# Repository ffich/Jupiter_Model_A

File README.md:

# Jupiter System
The Jupiter System is a system developed to leverage SW capabilities of Raspberry PI Compute Modules, by designing a system with an high level of HW configurability and scalability. This allows to use the power of the existing SW ecosystem in conjunction with a modular and scalable HW system, so that the user can take benefits from both of them. This HW configurability and expandability is given by adopting built-in sockets for some common peripheral add-on’s standard. The selected standards are the Mikroelektronika MikroBUS, the SeedStudio Grove and the Sparkfun QWIIC, which are widely used and open standards for HW expandability. The adherence to those standards allows the Jupiter System boards to be able to connect to the various expansion and breakout boards currently available on the market. These boards contain various types of sensor, actuators and interfaces, allowing for a very high level of HW scalability and modularity.

In this perspective the Jupiter System acts like a bridge between the Raspberry Pi SW and the HW world, allowing to take benefit from both the ecosystems.

Examples of application fields of Jupiter System are:
- Home automation System,
- IoT applications,
- Connectivity Applications,
- Monitoring and control Systems,
- Remote Control,
- Industrial Process control,
- Robotics applications,
- Test benches,
- Etc…

[youtube.com/watch?v=70Tqia20eaI](https://www.youtube.com/watch?v=70Tqia20eaI)

[youtube.com/watch?v=70Tqia20eaI](https://www.youtube.com/watch?v=70Tqia20eaI)

# Jupiter Model A
The Jupiter Model A is the desktop-version Jupiter board. It allows the user to experiment with the full potential of the Jupiter System. It's compatible with Raspberry CM3 and CM3+ (as the Raspberry Pi fundation does, we also strongly recommend to use CM3+ for newer design) and, among other peripherals, the board has 4 MikroBUS, 2 Grove and 2 Qwiic sockets that allow to create countless of combinations with Click, Grove or Qwiic slave devices.

# MikroE Click Boards
There are more that 1000 click boards currently available on the market, and so many applications can be realized exploiting the power of raspberry (on SW side) and the high availability and modularity of the click boards (on the HW side).
For more information on click boards, please refer to the Mikroe website: https://www.mikroe.com/click

# Board Description
The HW block diagram of the Jupiter Model A is depicted below. As is possible to see, the brain of the system is a Raspberry PI compute module 3 or 3+, connected to a broad list of peripherals. 

More in details, the board is populated with:
-	3x USB
-	1x WiFi
-	1x CSI Interface
-	1x DSI interface
-	1x Boot SD card Socket
-	1x Serial Port
-	Up to 16 GPIO
-	4x User LEDs
-	2x User Buttons

Additionally the board contains 4 MikroBUS Sockets that allow to interface with MikroBUS compatible devices, like the click boards, 2 Groove and 2 QWIIC connectors.

# Examples of combination with Click Boards

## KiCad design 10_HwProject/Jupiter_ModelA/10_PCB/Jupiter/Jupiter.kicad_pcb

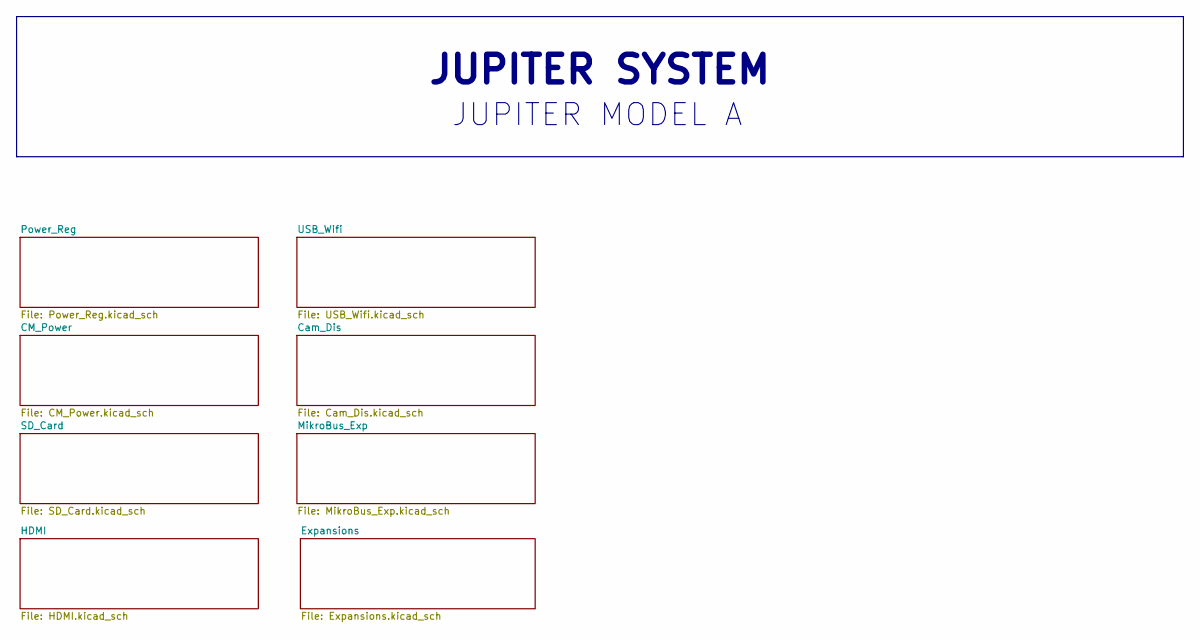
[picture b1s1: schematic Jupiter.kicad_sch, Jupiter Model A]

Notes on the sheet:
JUPITER SYSTEM
JUPITER MODEL A

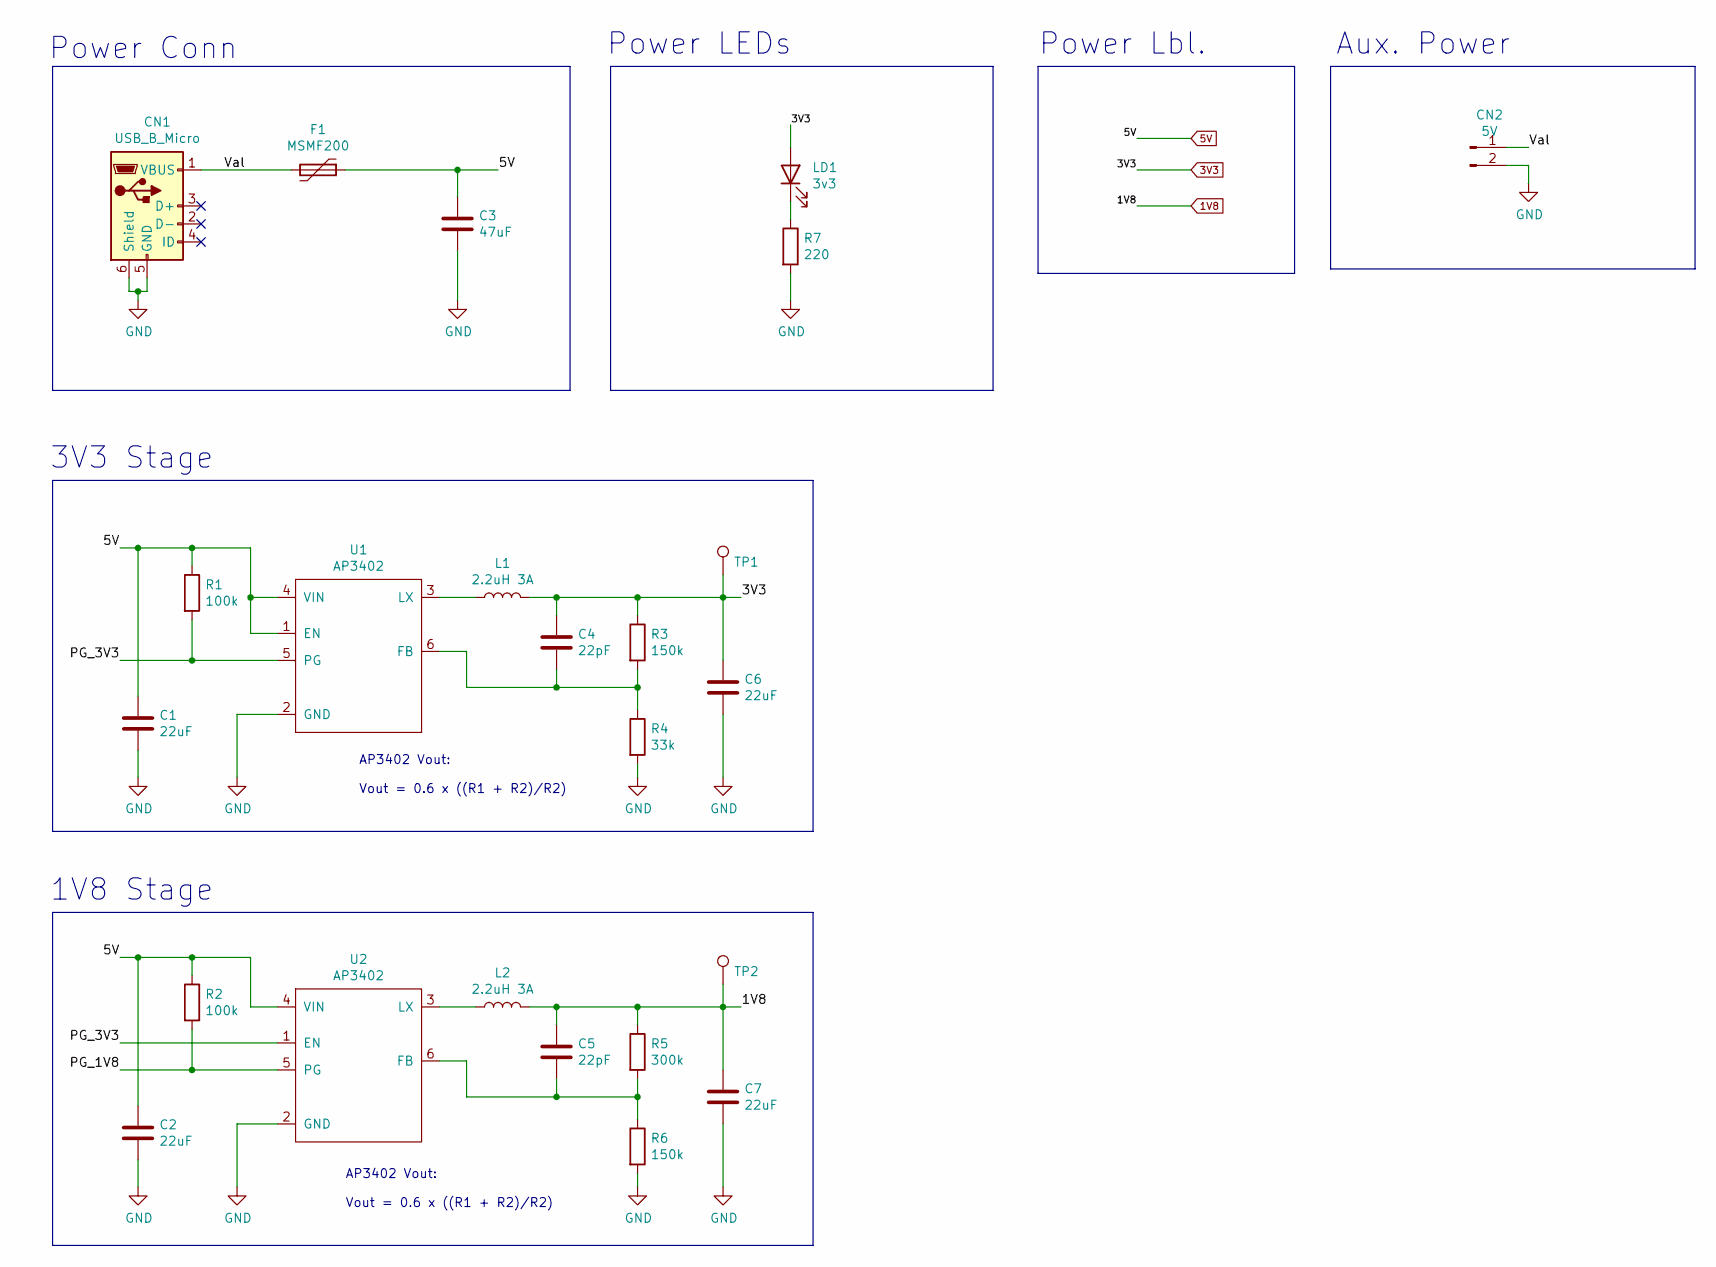
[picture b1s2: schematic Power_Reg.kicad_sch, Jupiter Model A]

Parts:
C1, C2, C6, C7: 22uF; C_0805_2012Metric
C3: 47uF; C_1206_3216Metric
C4, C5: 22pF; C_0603_1608Metric
CN1: USB_B_Micro; USB_Micro-B_Molex_47346-0001
CN2: 5V; PinHeader_1x02_P2.54mm_Vertical
F1: MSMF200; Fuse_1812_4532Metric
L1, L2: 2.2uH 3A; L_Sunlord_MWSA0518_5.4x5.2mm
LD1: 3v3; LED_0805_2012Metric
R1, R2: 100k; R_0603_1608Metric
R3, R6: 150k; R_0603_1608Metric
R4: 33k; R_0603_1608Metric
R5: 300k; R_0603_1608Metric
R7: 220; R_0603_1608Metric
TP1, TP2: TestPoint_Pad_D1.0mm
U1, U2: AP3402; TSOT-23-6

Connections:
1V8: C5.1, C7.1, L2.2, R5.1, TP2.1; also elsewhere on the board
3V3: C4.1, C6.1, L1.2, LD1.2 (A), R3.1, TP1.1; also elsewhere on the board
5V: C1.1, C2.1, C3.1, F1.1, R1.1, R2.1, U1.1 (EN), U1.4 (VIN), U2.4 (VIN); also elsewhere on the board
/Power_Reg/PG_1V8: R2.2, U2.5 (PG)
/Power_Reg/PG_3V3: R1.2, U1.5 (PG), U2.1 (EN)
/Power_Reg/Val: CN1.1 (VBUS), CN2.1, F1.2
GND: C1.2, C2.2, C3.2, C6.2, C7.2, CN1.5 (GND), CN1.6 (Shield), CN2.2, R4.2, R6.2, R7.2, U1.2 (GND), U2.2 (GND); also elsewhere on the board
unnamed: C4.2, R3.2, R4.1, U1.6 (FB)
unnamed: C5.2, R5.2, R6.1, U2.6 (FB)
unnamed: L1.1, U1.3 (LX)
unnamed: L2.1, U2.3 (LX)
unnamed: LD1.1 (K), R7.1

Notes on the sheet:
AP3402 Vout: Vout = 0.6 x ((R1 + R2)/R2)
Aux. Power
3V3 Stage
Power Lbl.
Power LEDs
Power Conn
1V8 Stage

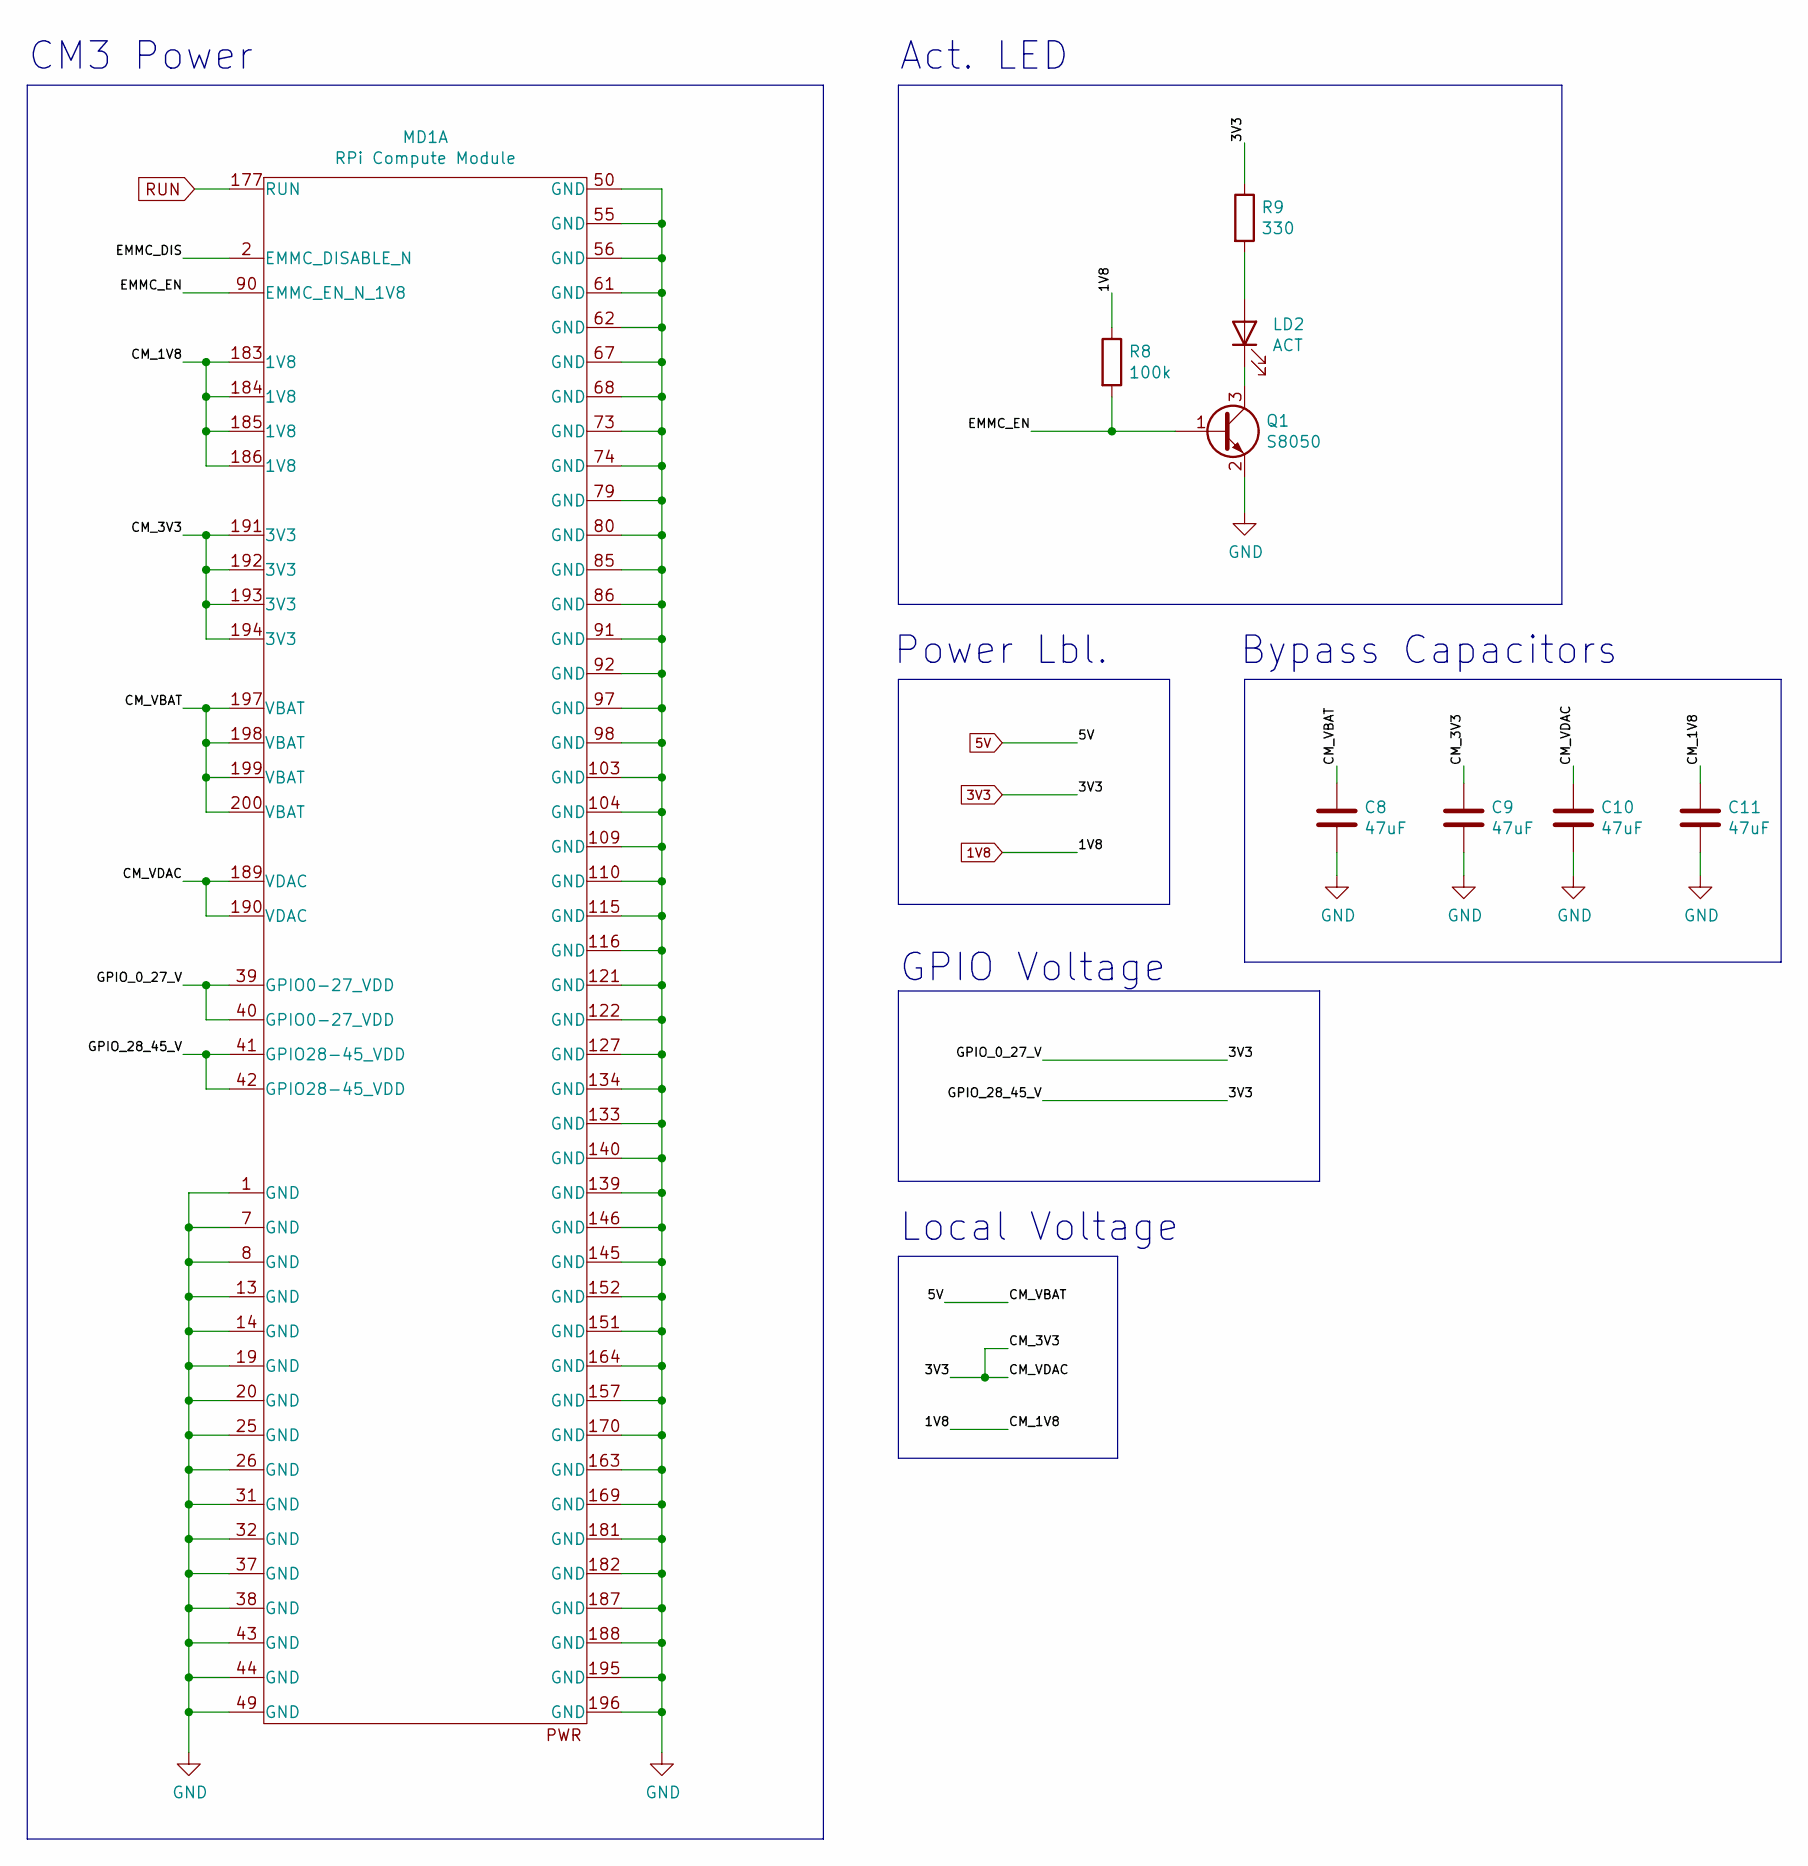
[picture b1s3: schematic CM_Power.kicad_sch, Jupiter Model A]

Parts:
C8, C9, C10, C11: 47uF; C_1206_3216Metric
LD2: ACT; LED_0805_2012Metric
MD1: RPi Compute Module; Conn_TE-DDR2-SODIMM-0.6-200P-doublesided
Q1: S8050; SOT-23
R8: 100k; R_0603_1608Metric
R9: 330; R_0603_1608Metric

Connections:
1V8: C11.1, MD1.183 (1V8), MD1.184 (1V8), MD1.185 (1V8), MD1.186 (1V8), R8.1; also elsewhere on the board
3V3: C9.1, C10.1, MD1.39 (GPIO0-27_VDD), MD1.40 (GPIO0-27_VDD), MD1.41 (GPIO28-45_VDD), MD1.42 (GPIO28-45_VDD), MD1.189 (VDAC), MD1.190 (VDAC), MD1.191 (3V3), MD1.192 (3V3), MD1.193 (3V3), MD1.194 (3V3), R9.1; also elsewhere on the board
5V: C8.1, MD1.197 (VBAT), MD1.198 (VBAT), MD1.199 (VBAT), MD1.200 (VBAT); also elsewhere on the board
/CM_Power/EMMC_DIS: MD1.2 (EMMC_DISABLE_N)
/CM_Power/EMMC_EN: MD1.90 (EMMC_EN_N_1V8), Q1.1 (B), R8.2
GND: C8.2, C9.2, C10.2, C11.2, MD1.1 (GND), MD1.7 (GND), MD1.8 (GND), MD1.13 (GND), MD1.14 (GND), MD1.19 (GND), MD1.20 (GND), MD1.25 (GND), MD1.26 (GND), MD1.31 (GND), MD1.32 (GND), MD1.37 (GND), MD1.38 (GND), MD1.43 (GND), MD1.44 (GND), MD1.49 (GND), MD1.50 (GND), MD1.55 (GND), MD1.56 (GND), MD1.61 (GND), MD1.62 (GND), MD1.67 (GND), MD1.68 (GND), MD1.73 (GND), MD1.74 (GND), MD1.79 (GND), MD1.80 (GND), MD1.85 (GND), MD1.86 (GND), MD1.91 (GND), MD1.92 (GND), MD1.97 (GND), MD1.98 (GND), MD1.103 (GND), MD1.104 (GND), MD1.109 (GND), MD1.110 (GND), MD1.115 (GND), MD1.116 (GND), MD1.121 (GND), MD1.122 (GND), MD1.127 (GND), MD1.133 (GND), MD1.134 (GND), MD1.139 (GND), MD1.140 (GND), MD1.145 (GND), MD1.146 (GND), MD1.151 (GND), MD1.152 (GND), MD1.157 (GND), MD1.163 (GND), MD1.164 (GND), MD1.169 (GND), MD1.170 (GND), MD1.181 (GND), MD1.182 (GND), MD1.187 (GND), MD1.188 (GND), MD1.195 (GND), MD1.196 (GND), Q1.2 (E); also elsewhere on the board
unnamed: LD2.1 (K), Q1.3 (C)
unnamed: LD2.2 (A), R9.2
RUN: MD1.177 (RUN); also elsewhere on the board

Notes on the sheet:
GPIO Voltage
Bypass Capacitors
Power Lbl.
CM3 Power
Act. LED
Local Voltage

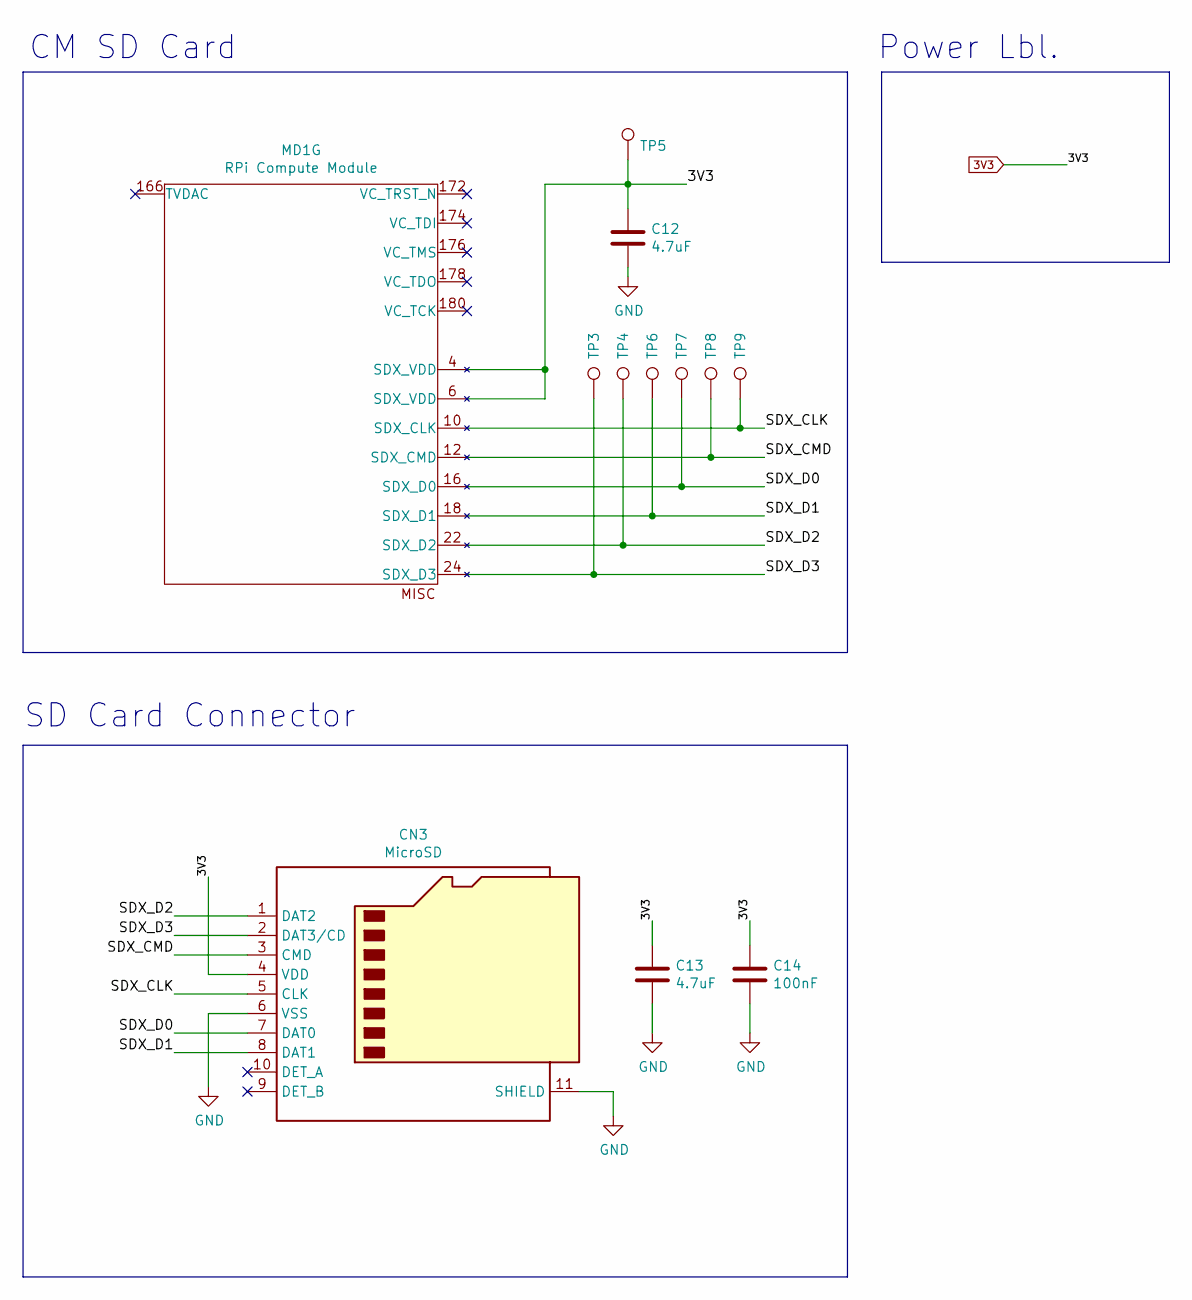
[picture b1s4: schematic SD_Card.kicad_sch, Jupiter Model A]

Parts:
C12, C13: 4.7uF; C_1206_3216Metric
C14: 100nF; C_0805_2012Metric
CN3: MicroSD; microSD_HC_Hirose_DM3D-SF
MD1: RPi Compute Module; Conn_TE-DDR2-SODIMM-0.6-200P-doublesided
TP3, TP4, TP5, TP6, TP7, TP8, TP9: TestPoint_Pad_D1.0mm

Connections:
3V3: C12.1, C13.1, C14.1, CN3.4 (VDD), MD1.4 (SDX_VDD), MD1.6 (SDX_VDD), TP5.1; also elsewhere on the board
/SD_Card/SDX_CLK: CN3.5 (CLK), MD1.10 (SDX_CLK), TP9.1
/SD_Card/SDX_CMD: CN3.3 (CMD), MD1.12 (SDX_CMD), TP8.1
/SD_Card/SDX_D0: CN3.7 (DAT0), MD1.16 (SDX_D0), TP7.1
/SD_Card/SDX_D1: CN3.8 (DAT1), MD1.18 (SDX_D1), TP6.1
/SD_Card/SDX_D2: CN3.1 (DAT2), MD1.22 (SDX_D2), TP4.1
/SD_Card/SDX_D3: CN3.2 (DAT3/CD), MD1.24 (SDX_D3), TP3.1
GND: C12.2, C13.2, C14.2, CN3.6 (VSS), CN3.11 (SHIELD); also elsewhere on the board

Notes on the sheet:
Power Lbl.
SD Card Connector
CM SD Card

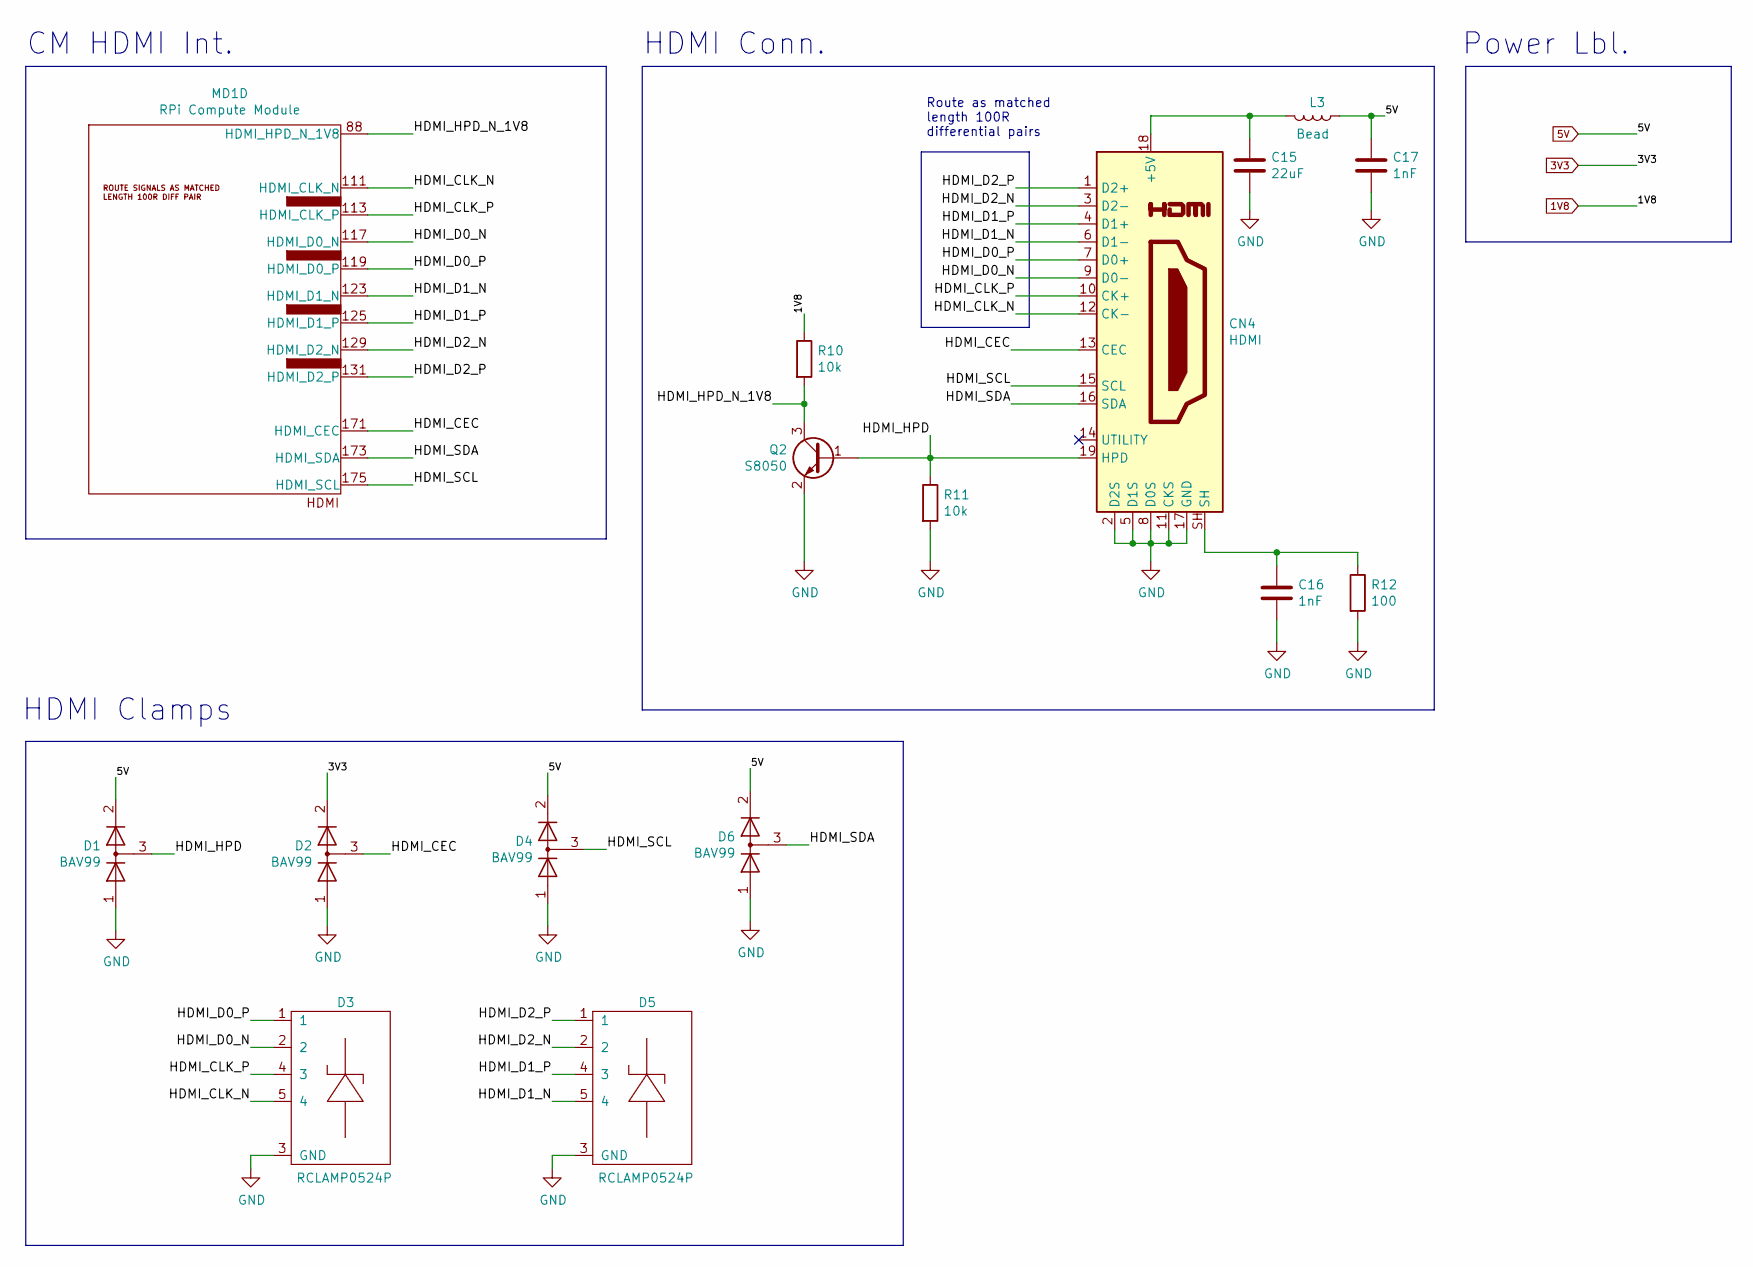
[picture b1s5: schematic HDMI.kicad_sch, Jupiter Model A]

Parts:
C15: 22uF; C_0805_2012Metric
C16: 1nF; C_0603_1608Metric
C17: 1nF; C_0805_2012Metric
CN4: HDMI; HDMI_TypeA
D1, D2, D4, D6: BAV99; SOT-23
D3, D5: RCLAMP0524P
L3: Bead; L_0805_2012Metric
MD1: RPi Compute Module; Conn_TE-DDR2-SODIMM-0.6-200P-doublesided
Q2: S8050; SOT-23
R10, R11: 10k; R_0603_1608Metric
R12: 100; R_0603_1608Metric

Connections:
1V8: R10.1; also elsewhere on the board
3V3: D2.2 (A); also elsewhere on the board
5V: C17.1, D1.2 (A), D4.2 (A), D6.2 (A), L3.1; also elsewhere on the board
/HDMI/HDMI_CEC: CN4.13 (CEC), D2.3 (K), MD1.171 (HDMI_CEC)
/HDMI/HDMI_CLK_N: CN4.12 (CK-), D3.5 (4), MD1.111 (HDMI_CLK_N)
/HDMI/HDMI_CLK_P: CN4.10 (CK+), D3.4 (3), MD1.113 (HDMI_CLK_P)
/HDMI/HDMI_D0_N: CN4.9 (D0-), D3.2, MD1.117 (HDMI_D0_N)
/HDMI/HDMI_D0_P: CN4.7 (D0+), D3.1, MD1.119 (HDMI_D0_P)
/HDMI/HDMI_D1_N: CN4.6 (D1-), D5.5 (4), MD1.123 (HDMI_D1_N)
/HDMI/HDMI_D1_P: CN4.4 (D1+), D5.4 (3), MD1.125 (HDMI_D1_P)
/HDMI/HDMI_D2_N: CN4.3 (D2-), D5.2, MD1.129 (HDMI_D2_N)
/HDMI/HDMI_D2_P: CN4.1 (D2+), D5.1, MD1.131 (HDMI_D2_P)
/HDMI/HDMI_HPD: CN4.19 (HPD), D1.3 (K), Q2.1 (B), R11.1
/HDMI/HDMI_HPD_N_1V8: MD1.88 (HDMI_HPD_N_1V8), Q2.3 (C), R10.2
/HDMI/HDMI_SCL: CN4.15 (SCL), D4.3 (K), MD1.175 (HDMI_SCL)
/HDMI/HDMI_SDA: CN4.16 (SDA), D6.3 (K), MD1.173 (HDMI_SDA)
GND: C15.2, C16.2, C17.2, CN4.2 (D2S), CN4.5 (D1S), CN4.8 (D0S), CN4.11 (CKS), CN4.17 (GND), D1.1 (K), D2.1 (K), D3.3 (GND), D4.1 (K), D5.3 (GND), D6.1 (K), Q2.2 (E), R11.2, R12.2; also elsewhere on the board
unnamed: C15.1, CN4.18 (+5V), L3.2
unnamed: C16.1, CN4.SH, R12.1

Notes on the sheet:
Power Lbl.
Route as matched length 100R differential pairs
HDMI Conn.
CM HDMI Int.
HDMI Clamps

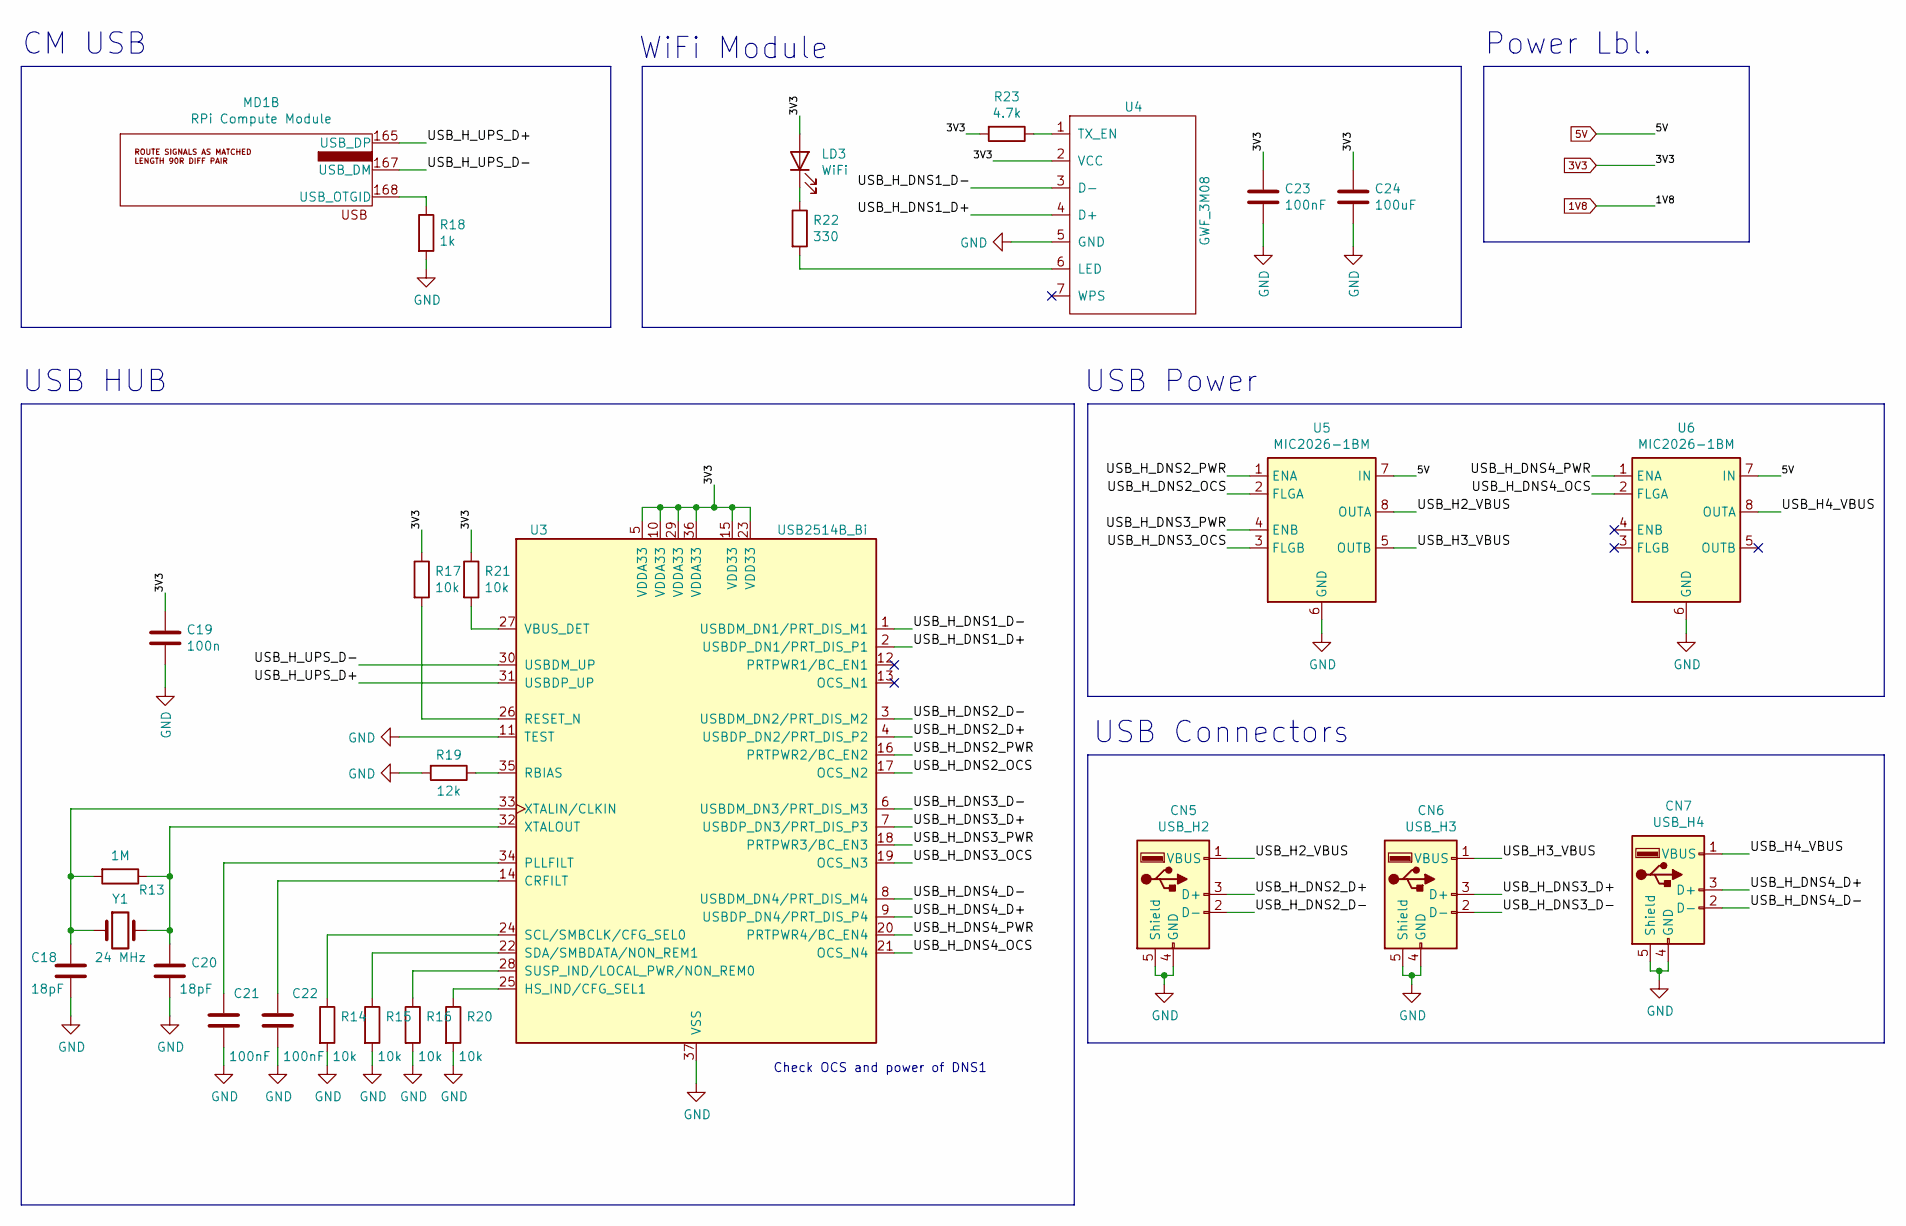
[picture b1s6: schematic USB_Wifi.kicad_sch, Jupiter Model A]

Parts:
C18, C20: 18pF; C_0603_1608Metric
C19: 100n; C_0805_2012Metric
C21, C22, C23: 100nF; C_0805_2012Metric
C24: 100uF; C_1206_3216Metric
CN5: USB_H2; USB_A_Stewart_SS-52100-001_Horizontal
CN6: USB_H3; USB_A_Stewart_SS-52100-001_Horizontal
CN7: USB_H4; USB_A_Stewart_SS-52100-001_Horizontal
LD3: WiFi; LED_0805_2012Metric
MD1: RPi Compute Module; Conn_TE-DDR2-SODIMM-0.6-200P-doublesided
R13: 1M; R_0603_1608Metric
R14, R15, R16, R17, R20, R21: 10k; R_0603_1608Metric
R18: 1k; R_0603_1608Metric
R19: 12k; R_0603_1608Metric
R22: 330; R_0603_1608Metric
R23: 4.7k; R_0603_1608Metric
U3: USB2514B_Bi; QFN-36-1EP_6x6mm_P0.5mm_EP3.7x3.7mm
U4: GWF_3M08; GWF_3M08_WifiModule
U5, U6: MIC2026-1BM; SOIC-8_3.9x4.9mm_P1.27mm
Y1: 24 MHz; Crystal_SMD_5032-2Pin_5.0x3.2mm

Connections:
3V3: C19.1, C23.1, C24.1, LD3.2 (A), R17.1, R21.1, R23.2, U3.5 (VDDA33), U3.10 (VDDA33), U3.15 (VDD33), U3.23 (VDD33), U3.29 (VDDA33), U3.36 (VDDA33), U4.2 (VCC); also elsewhere on the board
5V: U5.7 (IN), U6.7 (IN); also elsewhere on the board
/USB_Wifi/USB_H2_VBUS: CN5.1 (VBUS), U5.8 (OUTA)
/USB_Wifi/USB_H3_VBUS: CN6.1 (VBUS), U5.5 (OUTB)
/USB_Wifi/USB_H4_VBUS: CN7.1 (VBUS), U6.8 (OUTA)
/USB_Wifi/USB_H_DNS1_D+: U3.2 (USBDP_DN1/PRT_DIS_P1), U4.4 (D+)
/USB_Wifi/USB_H_DNS1_D-: U3.1 (USBDM_DN1/PRT_DIS_M1), U4.3 (D-)
/USB_Wifi/USB_H_DNS2_D+: CN5.3 (D+), U3.4 (USBDP_DN2/PRT_DIS_P2)
/USB_Wifi/USB_H_DNS2_D-: CN5.2 (D-), U3.3 (USBDM_DN2/PRT_DIS_M2)
/USB_Wifi/USB_H_DNS2_OCS: U3.17 (OCS_N2), U5.2 (FLGA)
/USB_Wifi/USB_H_DNS2_PWR: U3.16 (PRTPWR2/BC_EN2), U5.1 (ENA)
/USB_Wifi/USB_H_DNS3_D+: CN6.3 (D+), U3.7 (USBDP_DN3/PRT_DIS_P3)
/USB_Wifi/USB_H_DNS3_D-: CN6.2 (D-), U3.6 (USBDM_DN3/PRT_DIS_M3)
/USB_Wifi/USB_H_DNS3_OCS: U3.19 (OCS_N3), U5.3 (FLGB)
/USB_Wifi/USB_H_DNS3_PWR: U3.18 (PRTPWR3/BC_EN3), U5.4 (ENB)
/USB_Wifi/USB_H_DNS4_D+: CN7.3 (D+), U3.9 (USBDP_DN4/PRT_DIS_P4)
/USB_Wifi/USB_H_DNS4_D-: CN7.2 (D-), U3.8 (USBDM_DN4/PRT_DIS_M4)
/USB_Wifi/USB_H_DNS4_OCS: U3.21 (OCS_N4), U6.2 (FLGA)
/USB_Wifi/USB_H_DNS4_PWR: U3.20 (PRTPWR4/BC_EN4), U6.1 (ENA)
/USB_Wifi/USB_H_UPS_D+: MD1.165 (USB_DP), U3.31 (USBDP_UP)
/USB_Wifi/USB_H_UPS_D-: MD1.167 (USB_DM), U3.30 (USBDM_UP)
GND: C18.2, C19.2, C20.2, C21.2, C22.2, C23.2, C24.2, CN5.4 (GND), CN5.5 (Shield), CN6.4 (GND), CN6.5 (Shield), CN7.4 (GND), CN7.5 (Shield), R14.2, R15.2, R16.2, R18.2, R19.2, R20.2, U3.11 (TEST), U3.37 (VSS), U4.5 (GND), U5.6 (GND), U6.6 (GND); also elsewhere on the board
unnamed: C18.1, R13.2, U3.33 (XTALIN/CLKIN), Y1.1
unnamed: C20.1, R13.1, U3.32 (XTALOUT), Y1.2
unnamed: C21.1, U3.34 (PLLFILT)
unnamed: C22.1, U3.14 (CRFILT)
unnamed: LD3.1 (K), R22.1
unnamed: MD1.168 (USB_OTGID), R18.1
unnamed: R14.1, U3.24 (SCL/SMBCLK/CFG_SEL0)
unnamed: R15.1, U3.22 (SDA/SMBDATA/NON_REM1)
unnamed: R16.1, U3.28 (SUSP_IND/LOCAL_PWR/NON_REM0)
unnamed: R17.2, U3.26 (RESET_N)
unnamed: R19.1, U3.35 (RBIAS)
unnamed: R20.1, U3.25 (HS_IND/CFG_SEL1)
unnamed: R21.2, U3.27 (VBUS_DET)
unnamed: R22.2, U4.6 (LED)
unnamed: R23.1, U4.1 (TX_EN)

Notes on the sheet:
WiFi Module
USB Power
CM USB
Power Lbl.
USB HUB
Check OCS and power of DNS1
USB Connectors

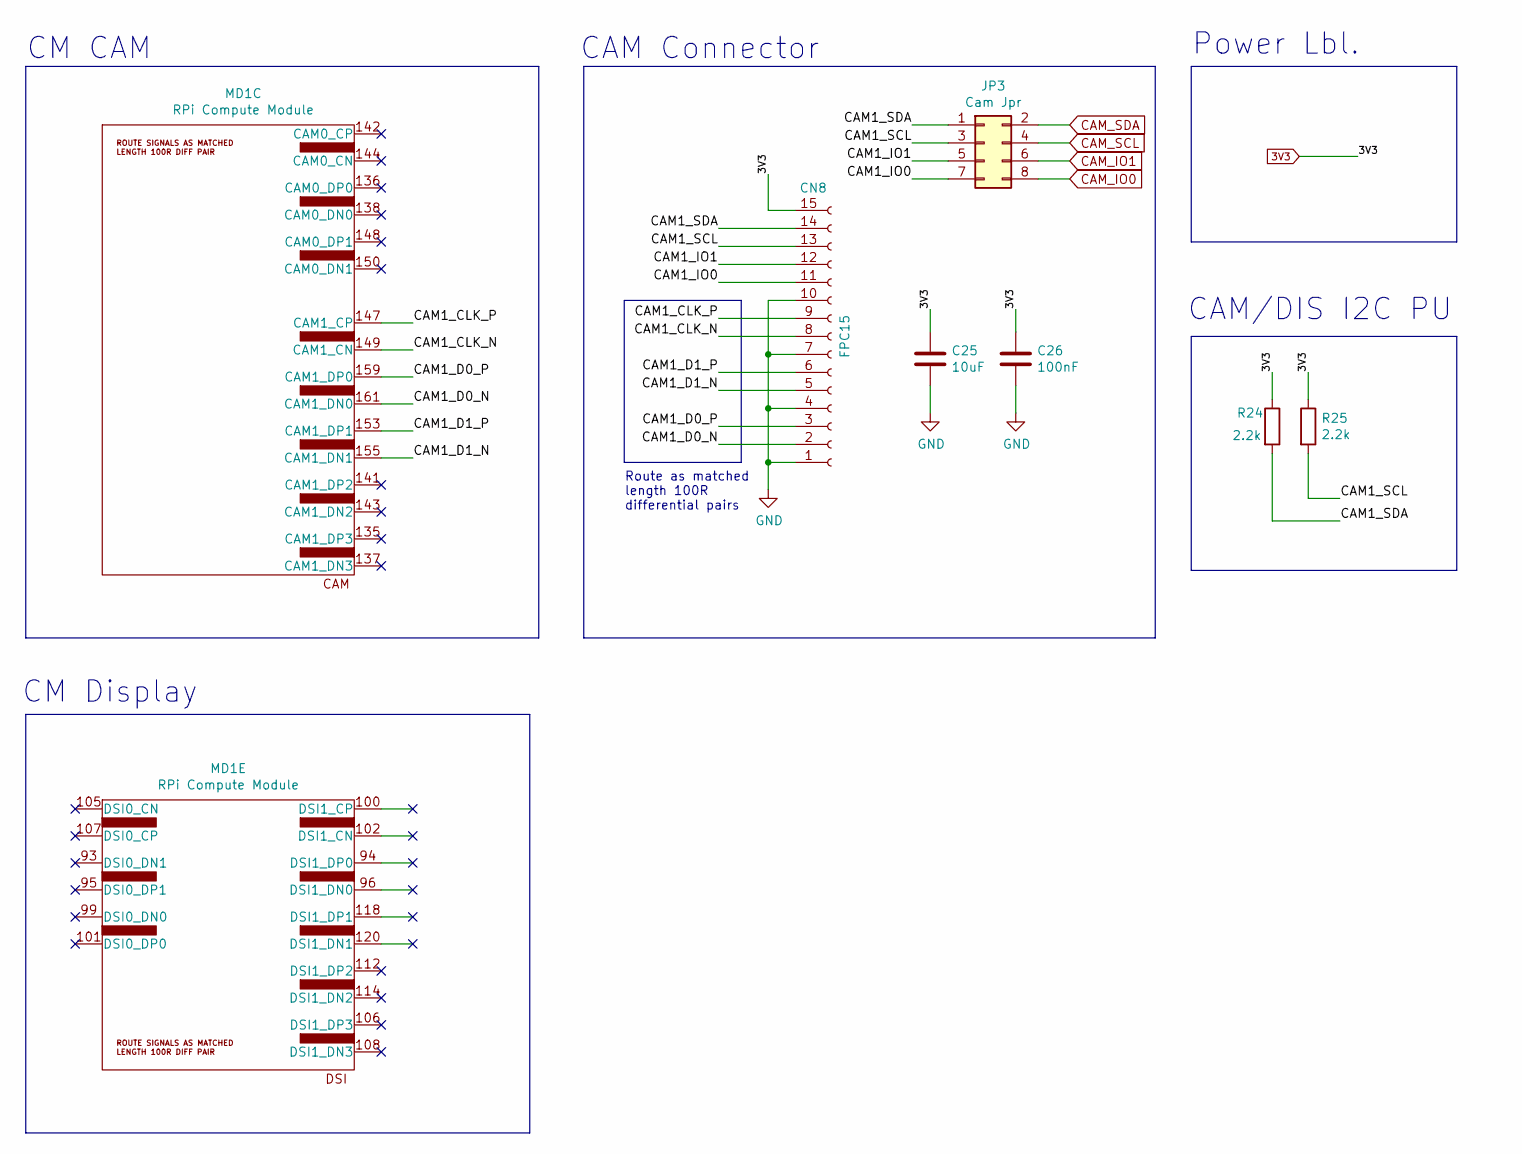
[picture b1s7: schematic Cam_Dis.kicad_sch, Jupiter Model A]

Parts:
C25: 10uF; C_1206_3216Metric
C26: 100nF; C_0805_2012Metric
CN8: FPC15; TE_1-84952-5_1x15-1MP_P1.0mm_Horizontal
JP3: Cam Jpr; PinHeader_2x04_P2.54mm_Vertical
MD1: RPi Compute Module; Conn_TE-DDR2-SODIMM-0.6-200P-doublesided
R24, R25: 2.2k; R_0603_1608Metric

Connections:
3V3: C25.1, C26.1, CN8.15, R24.1, R25.1; also elsewhere on the board
/Cam_Dis/CAM1_CLK_N: CN8.8, MD1.149 (CAM1_CN)
/Cam_Dis/CAM1_CLK_P: CN8.9, MD1.147 (CAM1_CP)
/Cam_Dis/CAM1_D0_N: CN8.2, MD1.161 (CAM1_DN0)
/Cam_Dis/CAM1_D0_P: CN8.3, MD1.159 (CAM1_DP0)
/Cam_Dis/CAM1_D1_N: CN8.5, MD1.155 (CAM1_DN1)
/Cam_Dis/CAM1_D1_P: CN8.6, MD1.153 (CAM1_DP1)
/Cam_Dis/CAM1_IO0: CN8.11, JP3.7
/Cam_Dis/CAM1_IO1: CN8.12, JP3.5
/Cam_Dis/CAM1_SCL: CN8.13, JP3.3, R25.2
/Cam_Dis/CAM1_SDA: CN8.14, JP3.1, R24.2
CAM_IO0: JP3.8; also elsewhere on the board
CAM_IO1: JP3.6; also elsewhere on the board
CAM_SCL: JP3.4; also elsewhere on the board
CAM_SDA: JP3.2; also elsewhere on the board
GND: C25.2, C26.2, CN8.1, CN8.4, CN8.7, CN8.10; also elsewhere on the board

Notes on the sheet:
CAM/DIS I2C PU
CAM Connector
CM Display
CM CAM
Power Lbl.
Route as matched length 100R differential pairs
